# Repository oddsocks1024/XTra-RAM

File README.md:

# XTra-RAM

## Description
512K RAM Expansion (8bit ISA) for XT class PCs and earlier with configurable banks

**Features**
* 512K RAM
* 8 x 64K banks
* Each bank can be independently configured as:
  * Low Address
  * High Address
  * Disabled

## Bill of Materials

| Qty | Component                        |
|:---:|----------------------------------|
| 16  | 10KΩ Axial Resistors - ¼ watt    |
| 1   | 74LS245 20pin DIP                |
| 2   | 74LS157 16pin DIP                |
| 1   | 74LS151 16pin DIP                |
| 1   | AS6C4008-55PCN SRAM 32pin DIP    |
| 5   | 100nF Ceramic Capacitors         |
| 2   | 47uF Electrolytic Capacitors     |
| 1   | 10uF Electrolytic Capacitor      |
| 2   | 8-Pole DIP switches              |

IC sockets optional.

## Usage
To configure the XTra-RAM correctly, it is important to have a basic understanding of the PC memory map, especially conventional memory.
It is also important to understand how much RAM you currently have installed, including on expansion cards.

The XTra-RAM contains 512K which is split into 8 x 64K memory banks. Each bank can either be mapped to a low address, a high address or disabled entirely.
This gives the card the best chance of working with many different memory configurations.

**Remember**

* RAM should be mapped contiguously into the address space. If there's a gap in the address space where no RAM is mapped, the PC will see no or less RAM.
* Never configure a memory bank on the XTra-RAM at both a high and low address. This will cause the same RAM to appear twice in the address space causing memory corruption.
* Never configure a memory bank on the XTra-RAM to be at the same address space as existing memory in the system, including other RAM expansions. This will cause a memory conflict.
* Configuring RAM in the UMA area is possible, but is very system specific and you should be careful not to conflict with expansions ROM etc.

### DIP Switches

| Memory Bank  | Enable Bank High      | Enable Bank Low       | Disable Bank	        | High Map Address      | Low Map Address |
|:------------:|-----------------------|-----------------------|------------------------|-----------------------|-----------------|
| 8            | SW2-8: ON, SW1-8: OFF | SW2-8: OFF, SW1-8: ON | SW2-8: OFF, SW1-8: OFF | F0000h - FFFFFh (UMA) | 70000h - 7FFFFh |
| 7            | SW2-7: ON, SW1-7: OFF | SW2-7: OFF, SW1-7: ON | SW2-8: OFF, SW1-8: OFF | E0000h - EFFFFh (UMA) | 60000h - 6FFFFh |
| 6            | SW2-7: ON, SW1-7: OFF | SW2-6: OFF, SW1-6: ON | SW2-8: OFF, SW1-8: OFF | D0000h - DFFFFh (UMA) | 50000h - 5FFFFh |
| 5            | SW2-7: ON, SW1-7: OFF | SW2-6: OFF, SW1-6: ON | SW2-8: OFF, SW1-8: OFF | C0000h - CFFFFh (UMA) | 40000h - 4FFFFh |
| 4            | SW2-7: ON, SW1-7: OFF | SW2-6: OFF, SW1-6: ON | SW2-8: OFF, SW1-8: OFF | B0000h - BFFFFh (UMA) | 30000h - 3FFFFh |
| 3            | SW2-7: ON, SW1-7: OFF | SW2-6: OFF, SW1-6: ON | SW2-8: OFF, SW1-8: OFF | A0000h - AFFFFh (UMA) | 20000h - 2FFFFh |
| 2            | SW2-7: ON, SW1-7: OFF | SW2-6: OFF, SW1-6: ON | SW2-8: OFF, SW1-8: OFF | 90000h - 9FFFFh       | 10000h - 1FFFFh |
| 1            | SW2-7: ON, SW1-7: OFF | SW2-6: OFF, SW1-6: ON | SW2-8: OFF, SW1-8: OFF | 80000h - 8FFFFh       | 00000h - 0FFFFh |

**NOTE:** Some systems have configuration jumpers on the motherboard which limit the amount of memory the BIOS will detect and this may prevent all or some of the additional memory from being seen. Consult the documentation for your system. 

### Example 1

An IBM 5150, populated with 64K on the motherboard. With the XTra-RAM we can provide a total of 576K, as follows:

* Bank 1 must be configured as High (if it was low, it would conflict with the motherboard memory)
* Banks 2 - 8 must be configured as Low

Resulting Memory Map

| Address         |                    |             |
|:---------------:|:------------------:|:-----------:|
| 00000h - 0FFFFh | Motherboard Memory | 0K - 64K    |
| 10000h - 1FFFFh | XTra-RAM Bank 2    | 64K - 128K  |
| 20000h - 2FFFFh | XTra-RAM Bank 3    | 128k - 192K |
| 30000h - 3FFFFh | XTra-RAM Bank 4    | 192K - 256K |
| 40000h - 4FFFFh | XTra-RAM Bank 5    | 256K - 320K |
| 50000h - 5FFFFh | XTra-RAM Bank 6    | 320K - 384K |
| 60000h - 6FFFFh | XTra-RAM Bank 7    | 384K - 448K |
| 70000h - 7FFFFh | XTra-RAM Bank 8    | 448K - 512K |
| 80000h - 8FFFFh | XTra-RAM Bank 1    | 512K - 576K |

### Example 2

An IBM 5150, populated with 64K on the motherboard and an IBM 256K RAM card (total 320K).

With the XTra-RAM we can provide a total of 640K, as follows:

* Bank 1 must be configured as High - If  low, it would conflict with the motherboard memory
* Bank 2 must be configured as High - If low, it would conflict with the IBM RAM Card
* Banks 3 - 5 must (* see note) be disabled - if low, they would conflict with the IBM RAM Card, if high they would be in the UMA area
* Banks 6 - 8 must be configured as Low

| Address         |                    |             |
|:---------------:|:------------------:|:-----------:|
| 00000h - 0FFFFh | Motherboard Memory | 0K - 64K    |
| 10000h - 1FFFFh | IBM RAM Card       | 64K - 128K  |
| 20000h - 2FFFFh | IBM RAM Card       | 128k - 192K |
| 30000h - 3FFFFh | IBM RAM Card       | 192K - 256K |
| 40000h - 4FFFFh | IBM RAM Card       | 256K - 320K |
| 50000h - 5FFFFh | XTra-RAM Bank 6    | 320K - 384K |
| 60000h - 6FFFFh | XTra-RAM Bank 7    | 384K - 448K |
| 70000h - 7FFFFh | XTra-RAM Bank 8    | 448K - 512K |
| 80000h - 8FFFFh | XTra-RAM Bank 1    | 512K - 576K |
| 90000h - 8FFFFh | XTra-RAM Bank 2    | 576K - 640K |

* It is possible to configure and use RAM in the UMA area, but this is very system configuration specific.

### Example 3

An XT, populated with 512K on the motherboard.

With the XTra-RAM we can provide a total of 640K, as follows:

* Banks 1 - 2 must be configured as High - If low, it would conflict with the motherboard memory
* Banks 3 - 8 must (* see note) be disabled - if low, they would conflict with the motherboard memory, if high, they would be in the UMA area

| Address         |                    |             |
|:---------------:|:------------------:|:-----------:|
| 00000h - 0FFFFh | Motherboard Memory | 0K - 64K    |
| 10000h - 1FFFFh | Motherboard Memory | 64K - 128K  |
| 20000h - 2FFFFh | Motherboard Memory | 128k - 192K |
| 30000h - 3FFFFh | Motherboard Memory | 192K - 256K |
| 40000h - 4FFFFh | Motherboard Memory | 256K - 320K |
| 50000h - 5FFFFh | Motherboard Memory | 320K - 384K |
| 60000h - 6FFFFh | Motherboard Memory | 384K - 448K |
| 70000h - 7FFFFh | Motherboard Memory | 448K - 512K |
| 80000h - 8FFFFh | XTra-RAM Bank 1    | 512K - 576K |
| 90000h - 8FFFFh | XTra-RAM Bank 2    | 576K - 640K |

* It is possible to configure and use RAM in the UMA area, but this is very system specific.

## Support Me
Everything is freely available so you can make your own PCB, however if you would like to support me, please see the following links.

* [My Projects](https://projects.amiga-hardware.com) - Donate on this page
* [Order the XTra-RAM PCB](https://www.pcbway.com/project/shareproject/XTra_RAM_512K_RAM_Card_for_XT_PCs_a331a696.html)

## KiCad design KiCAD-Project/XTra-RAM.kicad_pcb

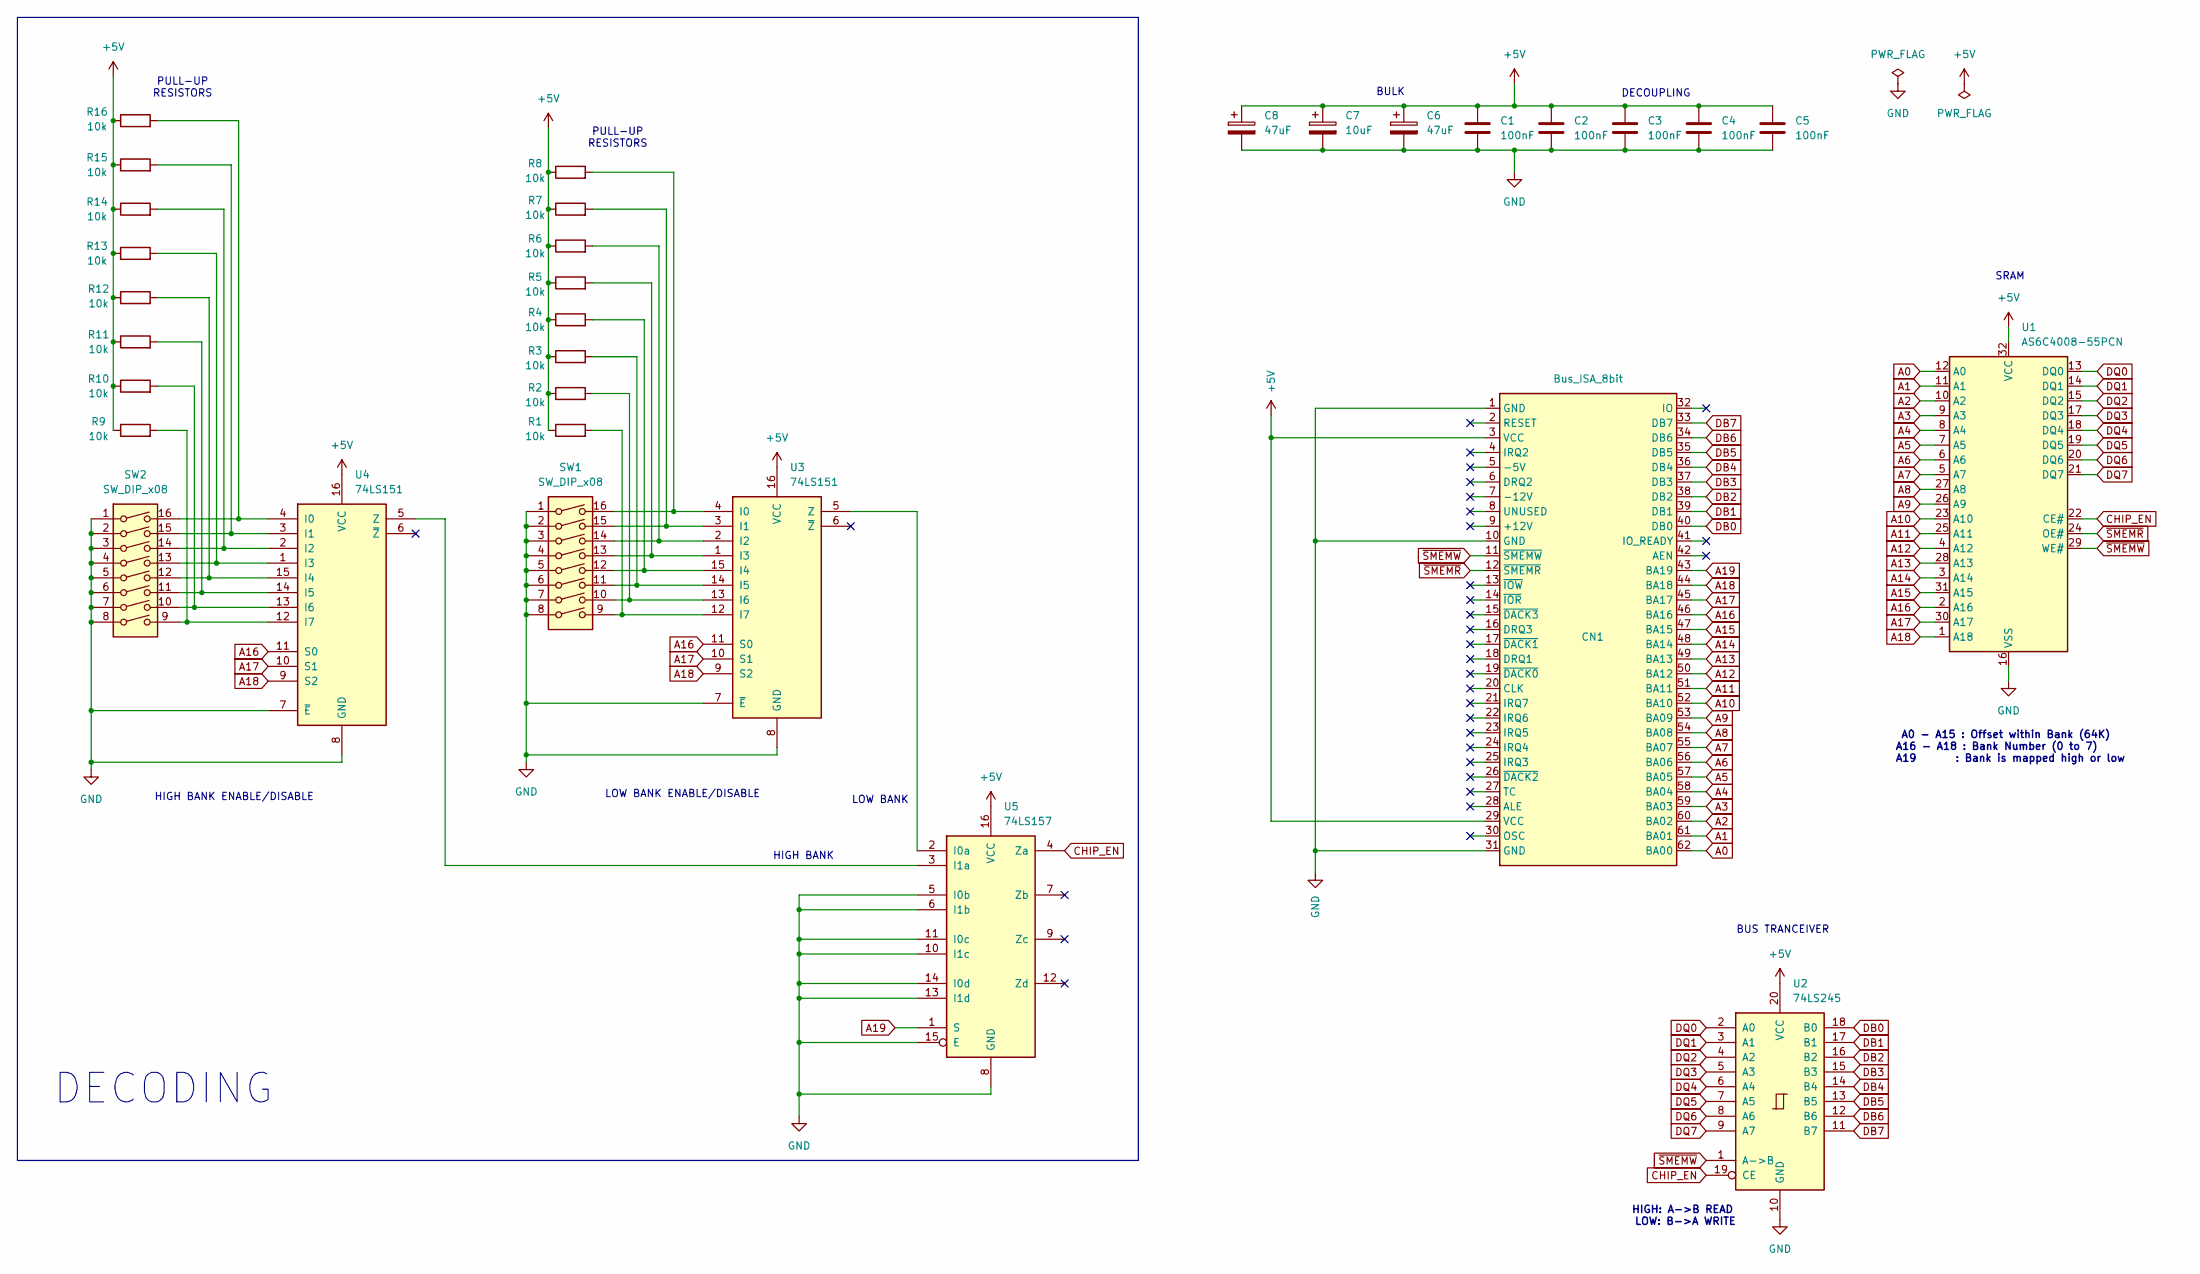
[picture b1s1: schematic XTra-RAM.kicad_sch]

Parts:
C1, C2, C3, C4, C5: 100nF; C_Disc_D5.0mm_W2.5mm_P5.00mm
C6, C8: 47uF; CP_Radial_D5.0mm_P2.50mm
C7: 10uF; CP_Radial_D5.0mm_P2.50mm
CN1: Bus_ISA_8bit; 8-bit ISA
R1, R2, R3, R4, R5, R6, R7, R8, R9, R10, R11, R12, R13, R14, R15, R16: 10k; R_Axial_DIN0207_L6.3mm_D2.5mm_P10.16mm_Horizontal
SW1, SW2: SW_DIP_x08; SW_DIP_SPSTx08_Slide_9.78x22.5mm_W7.62mm_P2.54mm
U1: AS6C4008-55PCN; DIP-32_W15.24mm
U2: 74LS245; DIP-20_W7.62mm_Socket
U3, U4: 74LS151; DIP-16_W7.62mm_Socket
U5: 74LS157; DIP-16_W7.62mm_Socket

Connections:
+5V: C1.1, C2.1, C3.1, C4.1, C5.1, C6.1, C7.1, C8.1, CN1.3 (VCC), CN1.29 (VCC), R1.1, R2.1, R3.1, R4.1, R5.1, R6.1, R7.1, R8.1, R9.1, R10.1, R11.1, R12.1, R13.1, R14.1, R15.1, R16.1, U1.32 (VCC), U2.20 (VCC), U3.16 (VCC), U4.16 (VCC), U5.16 (VCC)
A0: CN1.62 (BA00), U1.12 (A0)
A1: CN1.61 (BA01), U1.11 (A1)
A2: CN1.60 (BA02), U1.10 (A2)
A3: CN1.59 (BA03), U1.9 (A3)
A4: CN1.58 (BA04), U1.8 (A4)
A5: CN1.57 (BA05), U1.7 (A5)
A6: CN1.56 (BA06), U1.6 (A6)
A7: CN1.55 (BA07), U1.5 (A7)
A8: CN1.54 (BA08), U1.27 (A8)
A9: CN1.53 (BA09), U1.26 (A9)
A10: CN1.52 (BA10), U1.23 (A10)
A11: CN1.51 (BA11), U1.25 (A11)
A12: CN1.50 (BA12), U1.4 (A12)
A13: CN1.49 (BA13), U1.28 (A13)
A14: CN1.48 (BA14), U1.3 (A14)
A15: CN1.47 (BA15), U1.31 (A15)
A16: CN1.46 (BA16), U1.2 (A16), U3.11 (S0), U4.11 (S0)
A17: CN1.45 (BA17), U1.30 (A17), U3.10 (S1), U4.10 (S1)
A18: CN1.44 (BA18), U1.1 (A18), U3.9 (S2), U4.9 (S2)
A19: CN1.43 (BA19), U5.1 (S)
CHIP_EN: U1.22 (CE#), U2.19 (CE), U5.4 (Za)
DB0: CN1.40 (DB0), U2.18 (B0)
DB1: CN1.39 (DB1), U2.17 (B1)
DB2: CN1.38 (DB2), U2.16 (B2)
DB3: CN1.37 (DB3), U2.15 (B3)
DB4: CN1.36 (DB4), U2.14 (B4)
DB5: CN1.35 (DB5), U2.13 (B5)
DB6: CN1.34 (DB6), U2.12 (B6)
DB7: CN1.33 (DB7), U2.11 (B7)
DQ0: U1.13 (DQ0), U2.2 (A0)
DQ1: U1.14 (DQ1), U2.3 (A1)
DQ2: U1.15 (DQ2), U2.4 (A2)
DQ3: U1.17 (DQ3), U2.5 (A3)
DQ4: U1.18 (DQ4), U2.6 (A4)
DQ5: U1.19 (DQ5), U2.7 (A5)
DQ6: U1.20 (DQ6), U2.8 (A6)
DQ7: U1.21 (DQ7), U2.9 (A7)
GND: C1.2, C2.2, C3.2, C4.2, C5.2, C6.2, C7.2, C8.2, CN1.1 (GND), CN1.10 (GND), CN1.31 (GND), SW1.1, SW1.2, SW1.3, SW1.4, SW1.5, SW1.6, SW1.7, SW1.8, SW2.1, SW2.2, SW2.3, SW2.4, SW2.5, SW2.6, SW2.7, SW2.8, U1.16 (VSS), U2.10 (GND), U3.7 (~E), U3.8 (GND), U4.7 (~E), U4.8 (GND), U5.5 (I0b), U5.6 (I1b), U5.8 (GND), U5.10 (I1c), U5.11 (I0c), U5.13 (I1d), U5.14 (I0d), U5.15 (E)
unnamed: R8.2, SW1.16, U3.4 (I0)
unnamed: R7.2, SW1.15, U3.3 (I1)
unnamed: R6.2, SW1.14, U3.2 (I2)
unnamed: R5.2, SW1.13, U3.1 (I3)
unnamed: R4.2, SW1.12, U3.15 (I4)
unnamed: R3.2, SW1.11, U3.14 (I5)
unnamed: R2.2, SW1.10, U3.13 (I6)
unnamed: R1.2, SW1.9, U3.12 (I7)
unnamed: U3.5 (Z), U5.2 (I0a)
unnamed: R16.2, SW2.16, U4.4 (I0)
unnamed: R15.2, SW2.15, U4.3 (I1)
unnamed: R14.2, SW2.14, U4.2 (I2)
unnamed: R13.2, SW2.13, U4.1 (I3)
unnamed: R12.2, SW2.12, U4.15 (I4)
unnamed: R11.2, SW2.11, U4.14 (I5)
unnamed: R10.2, SW2.10, U4.13 (I6)
unnamed: R9.2, SW2.9, U4.12 (I7)
unnamed: U4.5 (Z), U5.3 (I1a)
~SMEMR: CN1.12 (~SMEMR), U1.24 (OE#)
~SMEMW: CN1.11 (~SMEMW), U1.29 (WE#), U2.1 (A->B)

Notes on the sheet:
DECODING
HIGH BANK ENABLE/DISABLE
LOW BANK
A0 - A15 : Offset within Bank (64K) A16 - A18 : Bank Number (0 to 7) A19 : Bank is mapped high or low
HIGH BANK
LOW BANK ENABLE/DISABLE
BUS TRANCEIVER
HIGH: A->B READ LOW: B->A WRITE
SRAM
PULL-UP RESISTORS
BULK
DECOUPLING

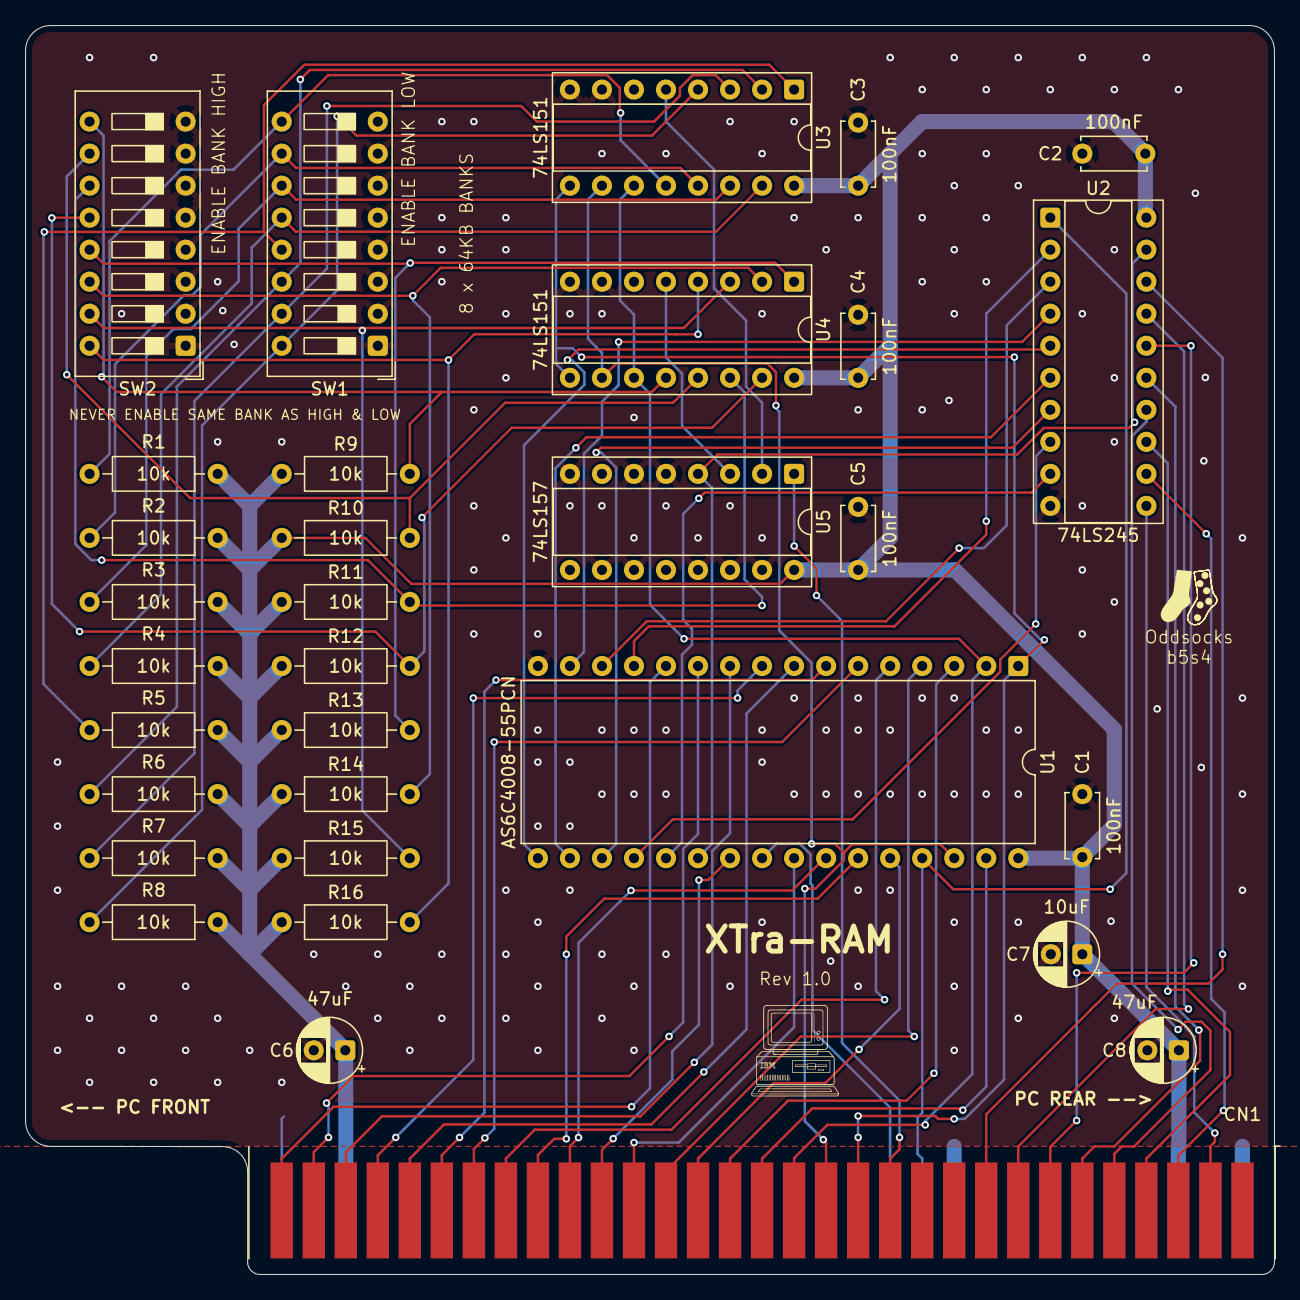
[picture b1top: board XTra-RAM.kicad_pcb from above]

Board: 2 copper layers, 99.1 x 99.1 mm, 32 parts (0 on the bottom side), 59 nets.

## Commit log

2025-11-29 Updated BOM
2025-11-29 Minor updates to schematic diagrams
2025-11-30 Add license file
2025-12-26 Fix some typos
